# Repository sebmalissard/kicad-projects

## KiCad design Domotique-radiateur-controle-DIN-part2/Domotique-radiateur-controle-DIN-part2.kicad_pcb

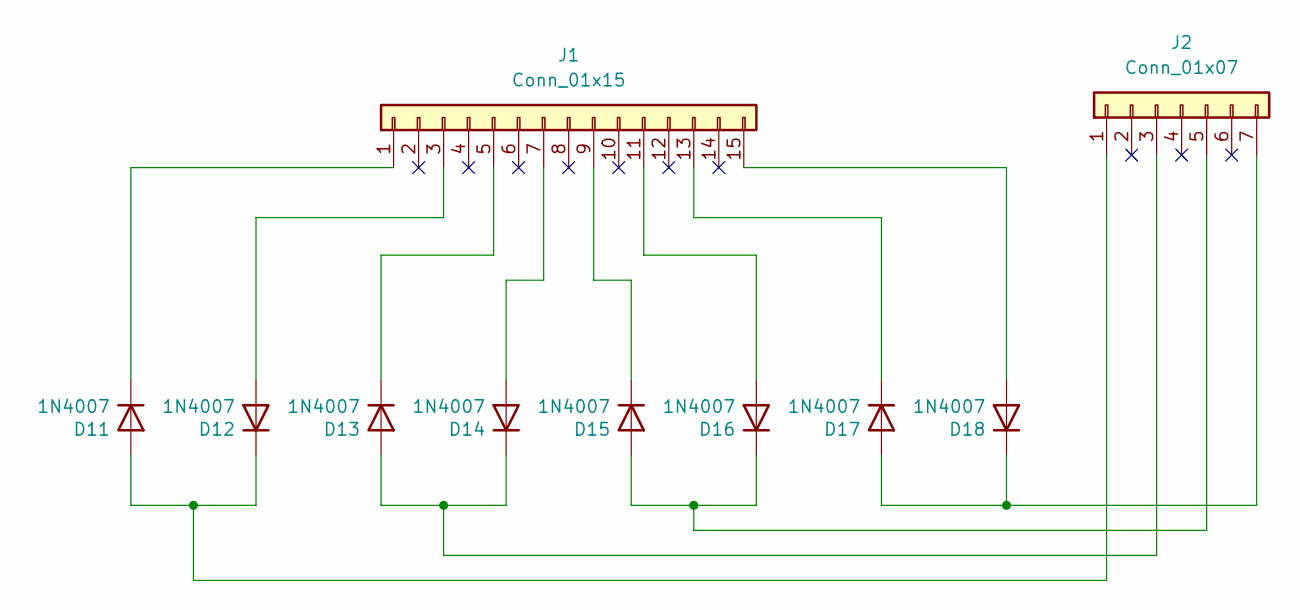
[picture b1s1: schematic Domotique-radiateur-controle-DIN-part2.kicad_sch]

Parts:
D11, D12, D13, D14, D15, D16, D17, D18: 1N4007; D_DO-41_SOD81_P7.62mm_Horizontal
J1: Conn_01x15; PinHeader_1x15_P2.54mm_Vertical
J2: Conn_01x07; PinHeader_1x07_P2.54mm_Vertical

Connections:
unnamed: D11.2 (A), D12.1 (K), J2.1
unnamed: D11.1 (K), J1.1
unnamed: D12.2 (A), J1.3
unnamed: D13.2 (A), D14.1 (K), J2.3
unnamed: D13.1 (K), J1.5
unnamed: D14.2 (A), J1.7
unnamed: D15.2 (A), D16.1 (K), J2.5
unnamed: D15.1 (K), J1.9
unnamed: D16.2 (A), J1.11
unnamed: D17.2 (A), D18.1 (K), J2.7
unnamed: D17.1 (K), J1.13
unnamed: D18.2 (A), J1.15

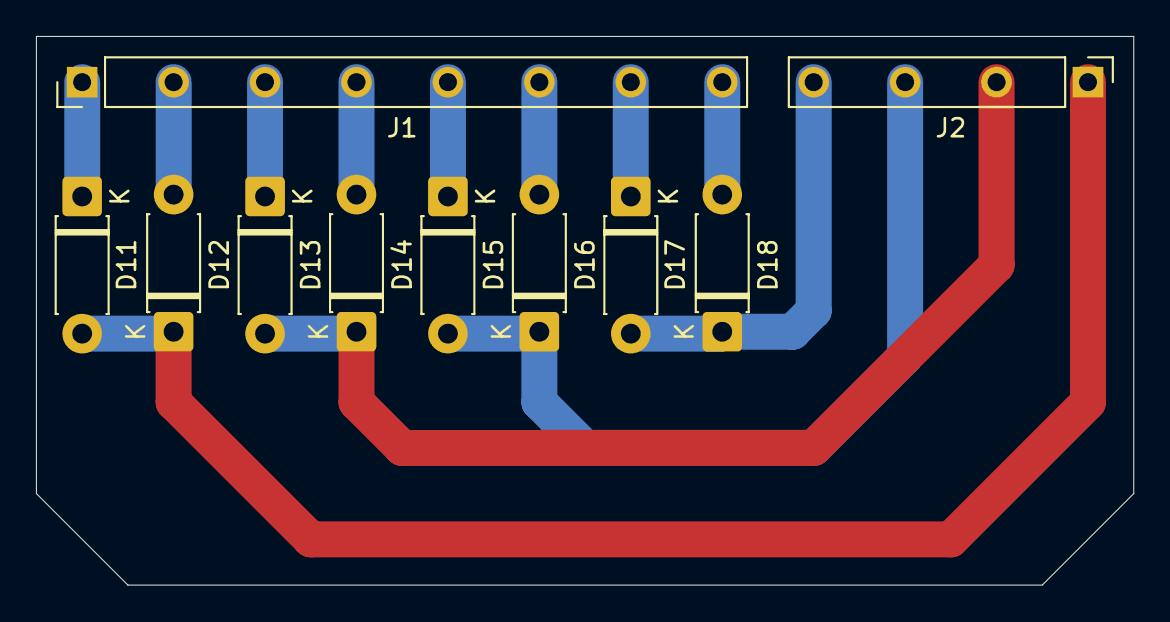
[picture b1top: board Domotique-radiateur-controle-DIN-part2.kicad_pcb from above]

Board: 2 copper layers, 61.0 x 30.5 mm, 10 parts (0 on the bottom side), 12 nets.

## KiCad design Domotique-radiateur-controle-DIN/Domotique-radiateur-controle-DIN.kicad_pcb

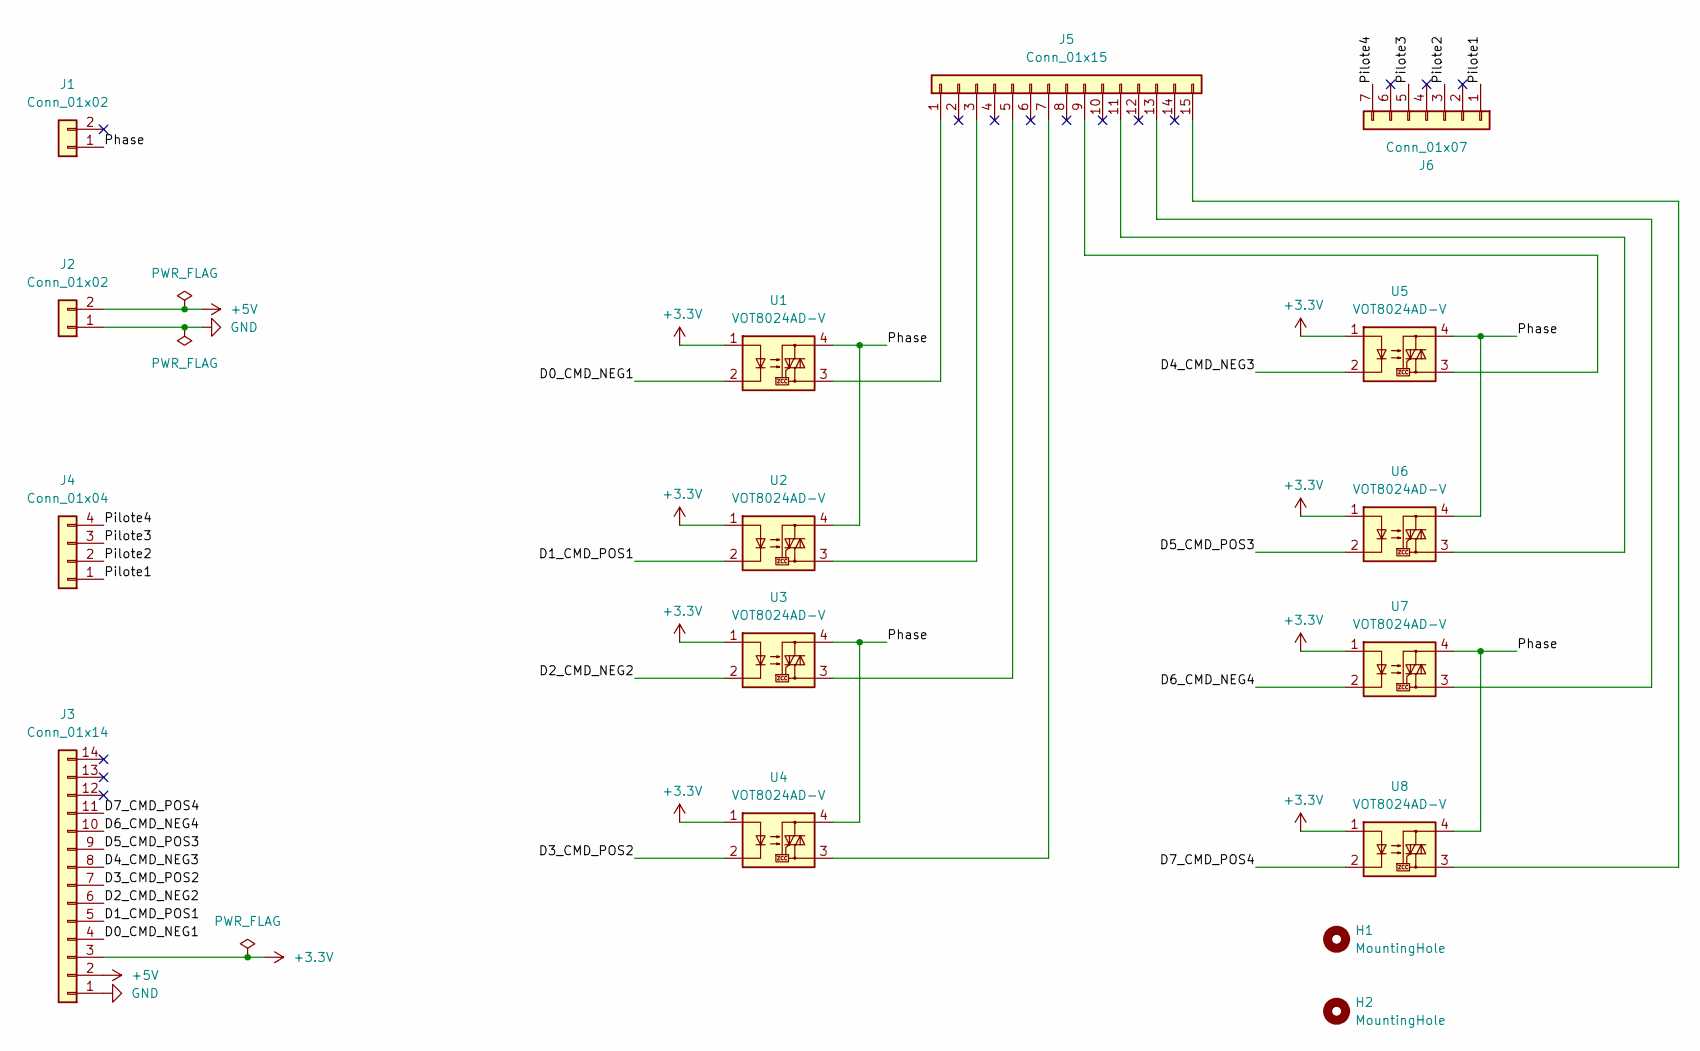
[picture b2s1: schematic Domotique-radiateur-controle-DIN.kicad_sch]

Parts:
H1, H2: MountingHole; MountingHole_3.2mm_M3
J1, J2: Conn_01x02; TerminalBlock_MetzConnect_Type055_RT01502HDWU_1x02_P5.00mm_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
J3: Conn_01x14; PinSocket_1x14_P2.54mm_Vertical
J4: Conn_01x04; TerminalBlock_MetzConnect_Type055_RT01504HDWU_1x04_P5.00mm_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
J5: Conn_01x15; PinHeader_1x15_P2.54mm_Vertical
J6: Conn_01x07; PinHeader_1x07_P2.54mm_Vertical
U1, U2, U3, U4, U5, U6, U7, U8: VOT8024AD-V; DIP-4_L6.5-W4.6-P2.54-LS7.6-BL; MPN VOT8024AD-V; LCSC Part C7149076

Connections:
+3.3V: J3.3, U1.1, U2.1, U3.1, U4.1, U5.1, U6.1, U7.1, U8.1
+5V: J2.2, J3.2
/D0_CMD_NEG1: J3.4, U1.2
/D1_CMD_POS1: J3.5, U2.2
/D2_CMD_NEG2: J3.6, U3.2
/D3_CMD_POS2: J3.7, U4.2
/D4_CMD_NEG3: J3.8, U5.2
/D5_CMD_POS3: J3.9, U6.2
/D6_CMD_NEG4: J3.10, U7.2
/D7_CMD_POS4: J3.11, U8.2
/Phase: J1.1 (Pin_1_1), U1.4, U2.4, U3.4, U4.4, U5.4, U6.4, U7.4, U8.4
/Pilote1: J4.1, J6.1
/Pilote2: J4.2, J6.3
/Pilote3: J4.3, J6.5
/Pilote4: J4.4, J6.7
GND: J2.1, J3.1
unnamed: J5.1, U1.3
unnamed: J5.3, U2.3
unnamed: J5.5, U3.3
unnamed: J5.7, U4.3
unnamed: J5.9, U5.3
unnamed: J5.11, U6.3
unnamed: J5.13, U7.3
unnamed: J5.15, U8.3

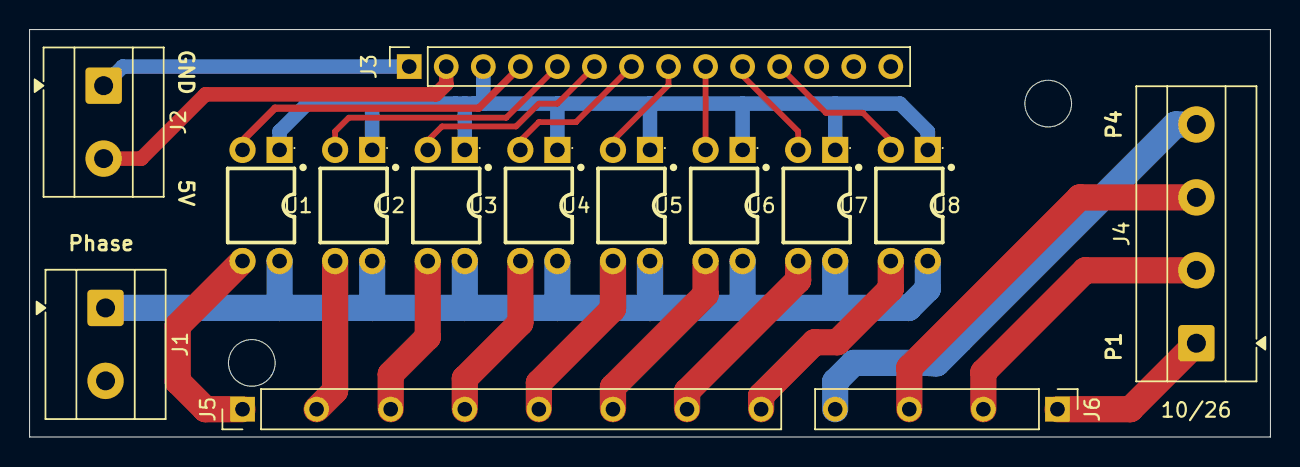
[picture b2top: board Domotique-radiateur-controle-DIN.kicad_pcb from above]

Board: 2 copper layers, 85.1 x 27.9 mm, 16 parts (0 on the bottom side), 24 nets.

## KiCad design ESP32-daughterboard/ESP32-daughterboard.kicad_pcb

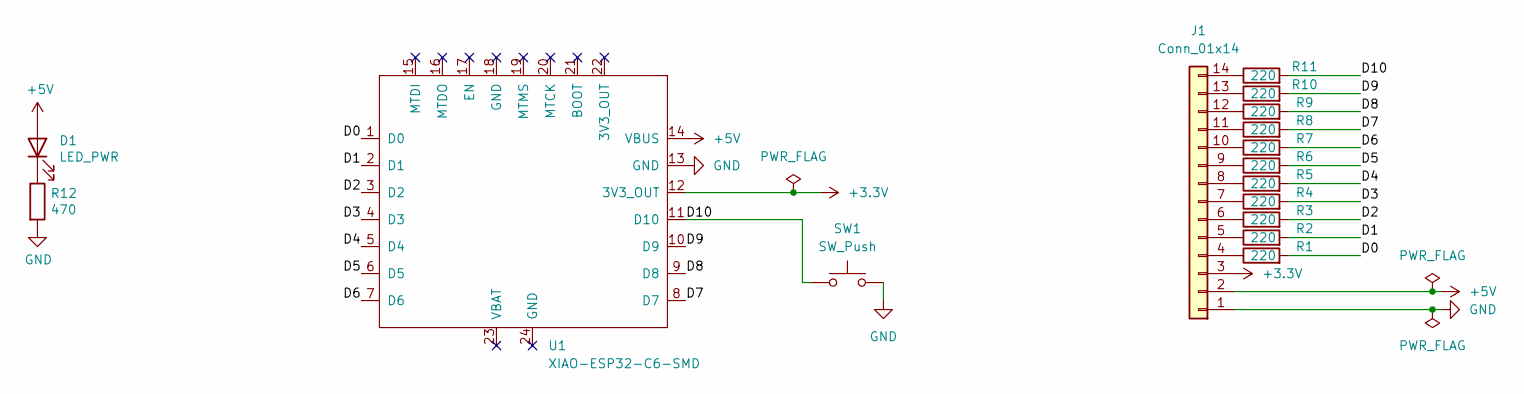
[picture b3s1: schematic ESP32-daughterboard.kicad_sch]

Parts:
D1: LED_PWR; LED_1206_3216Metric
J1: Conn_01x14; PinHeader_1x14_P2.54mm_Vertical
R1, R2, R3, R4, R5, R6, R7, R8, R9, R10, R11: 220; R_0805_2012Metric
R12: 470; R_Axial_DIN0207_L6.3mm_D2.5mm_P7.62mm_Horizontal
SW1: SW_Push
U1: XIAO-ESP32-C6-SMD; XIAO-ESP32-C6-DIP

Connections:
+3.3V: J1.3, U1.12 (3V3_OUT)
+5V: D1.2 (A), J1.2, U1.14 (VBUS)
/D0: R1.2, U1.1 (D0)
/D1: R2.2, U1.2 (D1)
/D2: R3.2, U1.3 (D2)
/D3: R4.2, U1.4 (D3)
/D4: R5.2, U1.5 (D4)
/D5: R6.2, U1.6 (D5)
/D6: R7.2, U1.7 (D6)
/D7: R8.2, U1.8 (D7)
/D8: R9.2, U1.9 (D8)
/D9: R10.2, U1.10 (D9)
/D10: R11.2, SW1.1, U1.11 (D10)
GND: J1.1, R12.2, SW1.2, U1.13 (GND)
unnamed: D1.1 (K), R12.1
unnamed: J1.4, R1.1
unnamed: J1.5, R2.1
unnamed: J1.6, R3.1
unnamed: J1.7, R4.1
unnamed: J1.8, R5.1
unnamed: J1.9, R6.1
unnamed: J1.10, R7.1
unnamed: J1.11, R8.1
unnamed: J1.12, R9.1
unnamed: J1.13, R10.1
unnamed: J1.14, R11.1

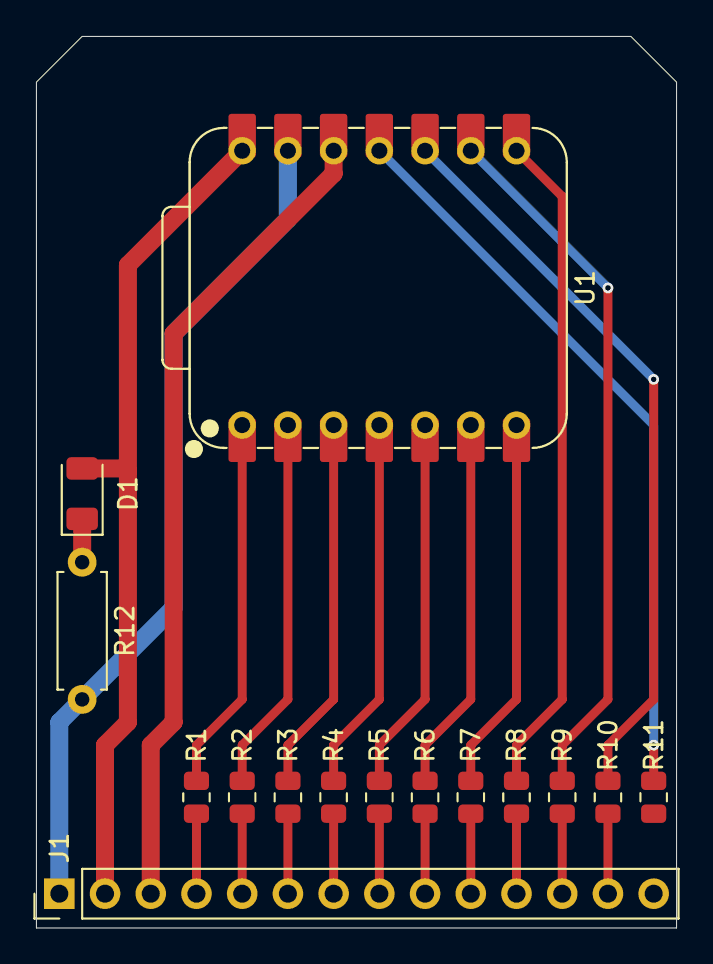
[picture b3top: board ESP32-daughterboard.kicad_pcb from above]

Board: 2 copper layers, 35.6 x 49.5 mm, 15 parts (0 on the bottom side), 26 nets.

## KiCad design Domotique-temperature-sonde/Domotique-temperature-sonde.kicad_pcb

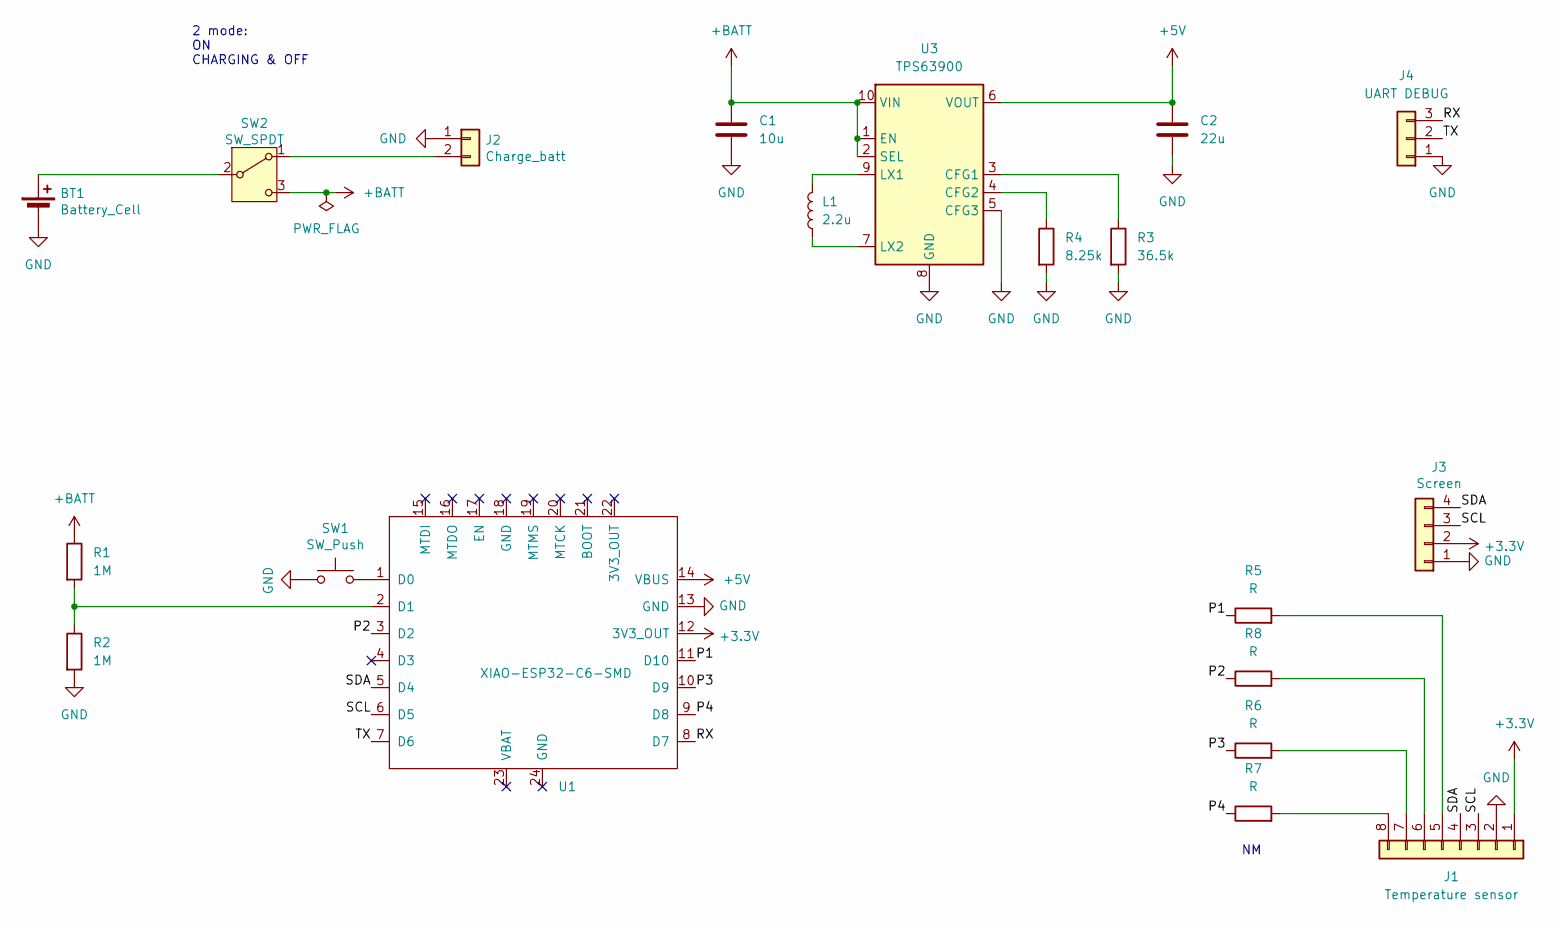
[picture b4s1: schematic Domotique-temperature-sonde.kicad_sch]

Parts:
BT1: Battery_Cell; Battery 18650
C1: 10u; C_0603_1608Metric; LCSC Part # C19702
C2: 22u; C_1206_3216Metric; LCSC Part # C12891
J1: Temperature sensor; PinSocket_1x08_P2.54mm_Horizontal
J2: Charge_batt; Molex_Micro-Fit_3.0_43650-0203_1x02_P3.00mm_Horizontal
J3: Screen; Display oled 0.91
J4: UART DEBUG; PinSocket_1x03_P2.54mm_Horizontal
L1: 2.2u; L_1008_2520Metric; LCSC Part # C576403
R1, R2: 1M; R_0805_2012Metric; LCSC Part # C17514
R3: 36.5k; R_0805_2012Metric; LCSC Part # C218534
R4: 8.25k; R_0805_2012Metric; LCSC Part # C374739
R5, R6, R7, R8: R; R_0805_2012Metric
SW1: SW_Push; SW_PUSH_6mm_H5mm
SW2: SW_SPDT; SW_Slide_SPDT_Angled_SK12F14VG4_3mm
U1: XIAO-ESP32-C6-SMD; XIAO-ESP32-C6-DIP
U3: TPS63900; WSON-10-1EP_2.5x2.5mm_P0.5mm_EP1.2x2mm_ThermalVias; LCSC Part # C1518762

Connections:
+3.3V: J1.1, J3.2, U1.12 (3V3_OUT)
+5V: C2.1, U1.14 (VBUS), U3.6 (VOUT)
+BATT: C1.1, R1.1, SW2.3 (C), U3.1 (EN), U3.2 (SEL), U3.10 (VIN)
/P1: R5.1, U1.11 (D10)
/P2: R8.1, U1.3 (D2)
/P3: R6.1, U1.10 (D9)
/P4: R7.1, U1.9 (D8)
/RX: J4.3, U1.8 (D7)
/SCL: J1.3, J3.3, U1.6 (D5)
/SDA: J1.4, J3.4, U1.5 (D4)
/TX: J4.2, U1.7 (D6)
GND: BT1.2 (-), C1.2, C2.2, J1.2, J2.1, J3.1, J4.1, R2.2, R3.2, R4.2, SW1.1, U1.13 (GND), U3.5 (CFG3), U3.8 (GND), U3.11 (GND)
unnamed: BT1.1 (+), SW2.2 (B)
unnamed: J1.5, R5.2
unnamed: J1.6, R8.2
unnamed: J1.7, R6.2
unnamed: J1.8, R7.2
unnamed: J2.2, SW2.1 (A)
unnamed: SW1.2, U1.1 (D0)
unnamed: R1.2, R2.1, U1.2 (D1)
unnamed: R3.1, U3.3 (CFG1)
unnamed: R4.1, U3.4 (CFG2)
unnamed: L1.2, U3.9 (LX1)
unnamed: L1.1, U3.7 (LX2)

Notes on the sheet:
2 mode: ON CHARGING & OFF

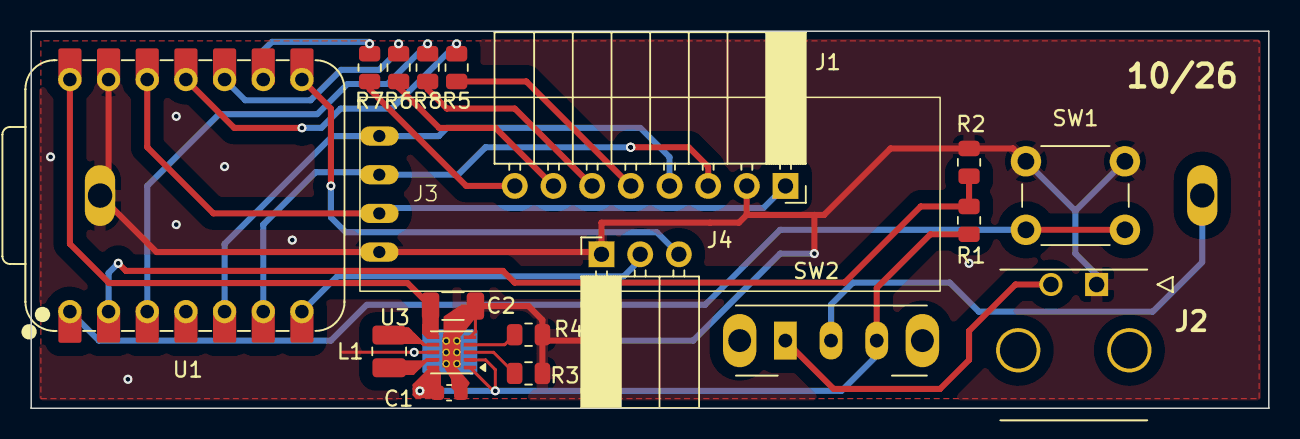
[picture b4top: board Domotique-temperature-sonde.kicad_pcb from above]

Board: 2 copper layers, 81.3 x 24.8 mm, 20 parts (1 on the bottom side), 24 nets.

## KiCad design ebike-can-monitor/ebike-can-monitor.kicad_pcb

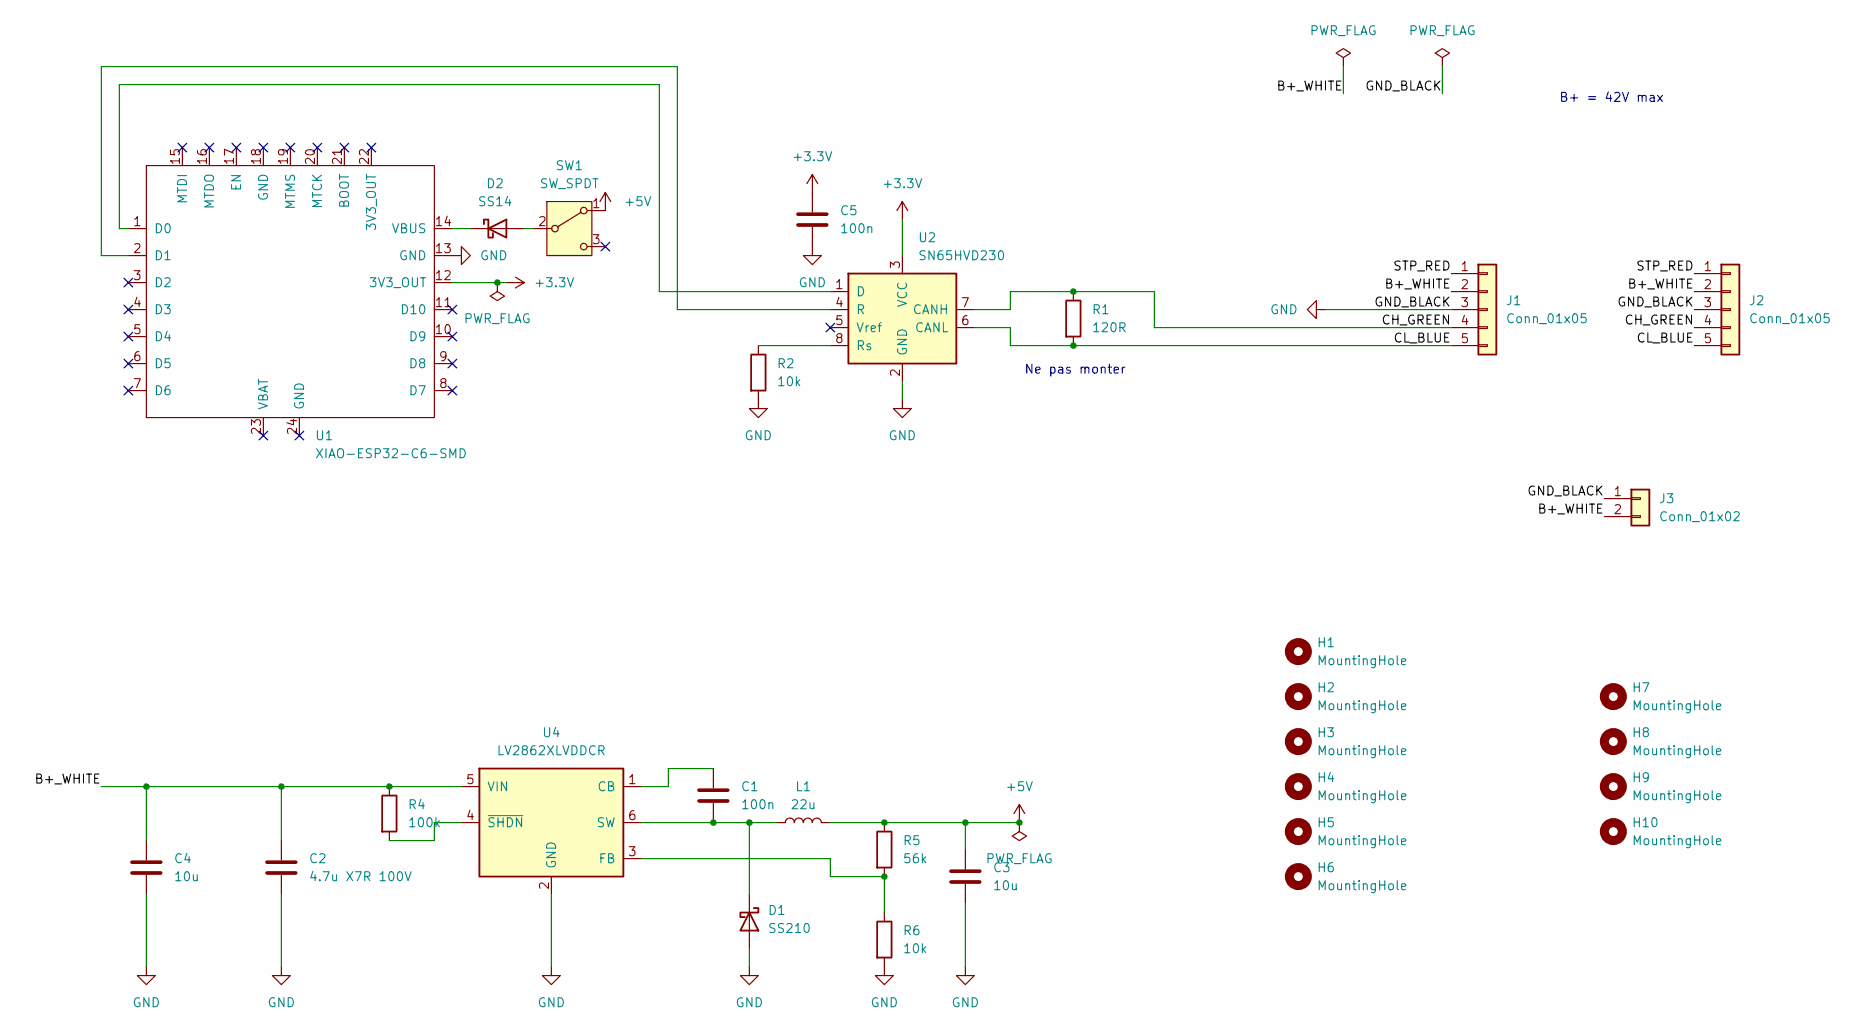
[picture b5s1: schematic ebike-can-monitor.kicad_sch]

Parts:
C1, C5: 100n; C_0805_2012Metric; LCSC C28233
C2: 4.7u X7R 100V; C_1206_3216Metric; LCSC C29823
C3, C4: 10u; C_1206_3216Metric; LCSC C13585
D1: SS210; D_SMA; LCSC C14996
D2: SS14; D_SMA; LCSC C2480
H1, H2, H3, H4, H5, H6, H7, H8, H9, H10: MountingHole; MountingHole_3.2mm_M3
J1, J2: Conn_01x05; PinHeader_1x05_P2.54mm_Vertical
J3: Conn_01x02; Molex_Micro-Fit_3.0_43650-0203_1x02_P3.00mm_Horizontal
L1: 22u; IND-SMD_L4.0-W4.0_LVF4040XX; LCSC C910042
R1: 120R; R_1206_3216Metric
R2, R6: 10k; R_0603_1608Metric; LCSC C25804
R4: 100k; R_0603_1608Metric; LCSC C25803
R5: 56k; R_0603_1608Metric; LCSC C23206
SW1: SW_SPDT; SW_Slide_SPDT_Straight_2D00G_3mm
U1: XIAO-ESP32-C6-SMD; XIAO-ESP32-C6-DIP
U2: SN65HVD230; SOIC-8_3.9x4.9mm_P1.27mm; LCSC C12084
U4: LV2862XLVDDCR; SOT-23-6; LCSC C3200285

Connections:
+3.3V: C5.1, U1.12 (3V3_OUT), U2.3 (VCC)
+5V: C3.1, L1.2, R5.1, SW1.1 (A)
/B+_WHITE: C2.1, C4.1, J1.2, J2.2, J3.2, R4.1, U4.5 (VIN)
/CH_GREEN: J1.4, J2.4, R1.1, U2.7 (CANH)
/CL_BLUE: J1.5, J2.5, R1.2, U2.6 (CANL)
/STP_RED: J1.1, J2.1
GND: C2.2, C3.2, C4.2, C5.2, D1.2 (A), J1.3, J2.3, J3.1, R2.2, R6.2, U1.13 (GND), U2.2 (GND), U4.2 (GND)
unnamed: C1.2, D1.1 (K), L1.1, U4.6 (SW)
unnamed: D2.2 (A), SW1.2 (B)
unnamed: D2.1 (K), U1.14 (VBUS)
unnamed: U1.1 (D0), U2.1 (D)
unnamed: U1.2 (D1), U2.4 (R)
unnamed: R2.1, U2.8 (Rs)
unnamed: C1.1, U4.1 (CB)
unnamed: R5.2, R6.1, U4.3 (FB)
unnamed: R4.2, U4.4 (~SHDN)

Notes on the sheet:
B+ = 42V max
Ne pas monter

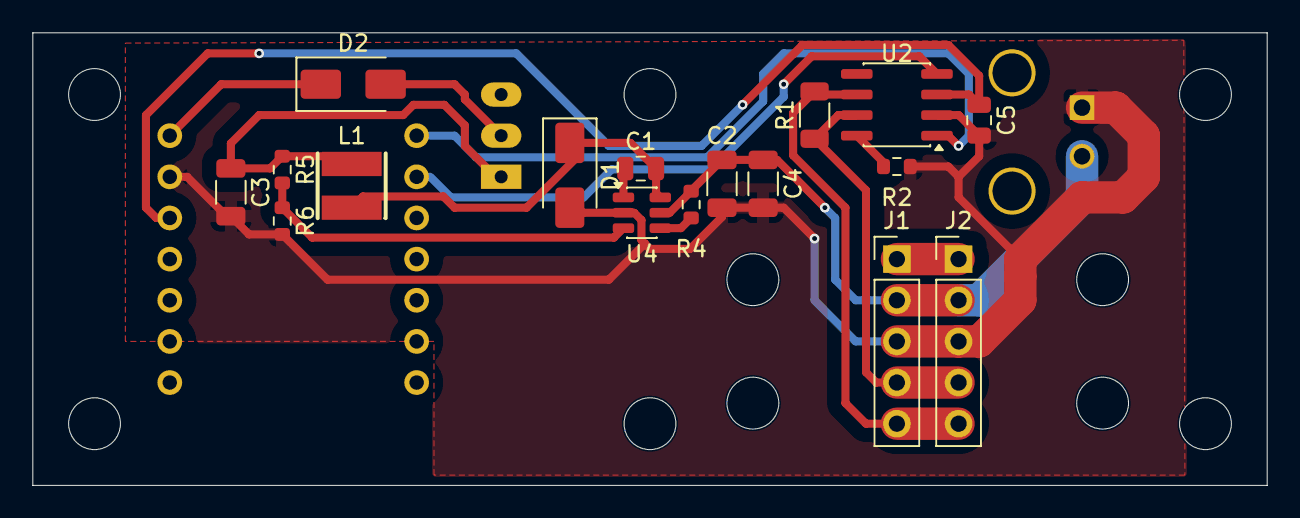
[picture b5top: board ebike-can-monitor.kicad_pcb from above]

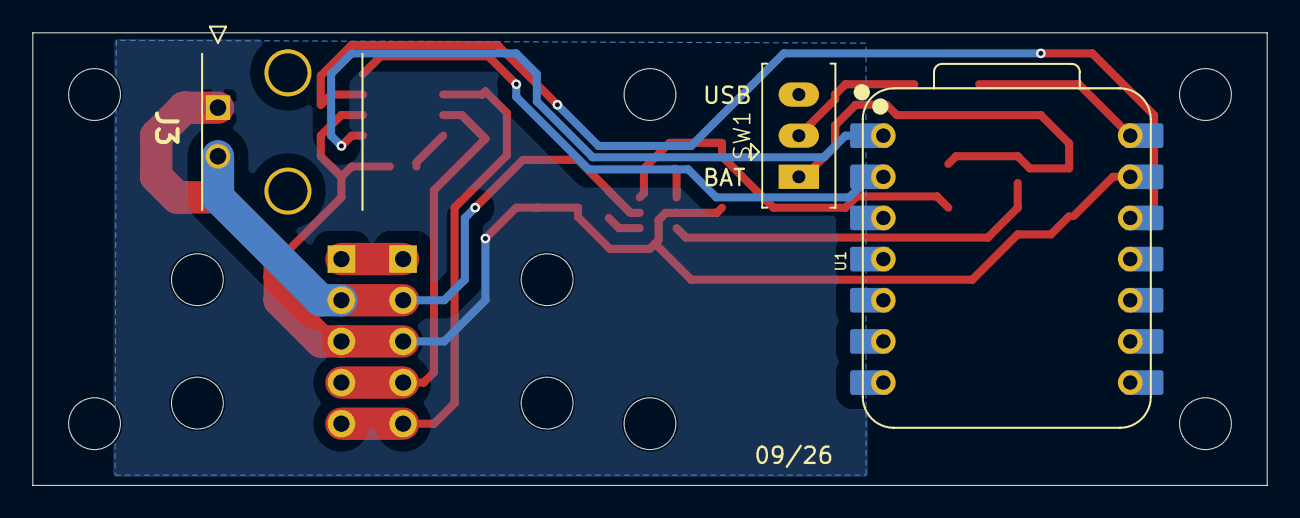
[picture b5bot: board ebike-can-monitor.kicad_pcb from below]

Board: 2 copper layers, 76.2 x 27.9 mm, 30 parts (3 on the bottom side), 16 nets.

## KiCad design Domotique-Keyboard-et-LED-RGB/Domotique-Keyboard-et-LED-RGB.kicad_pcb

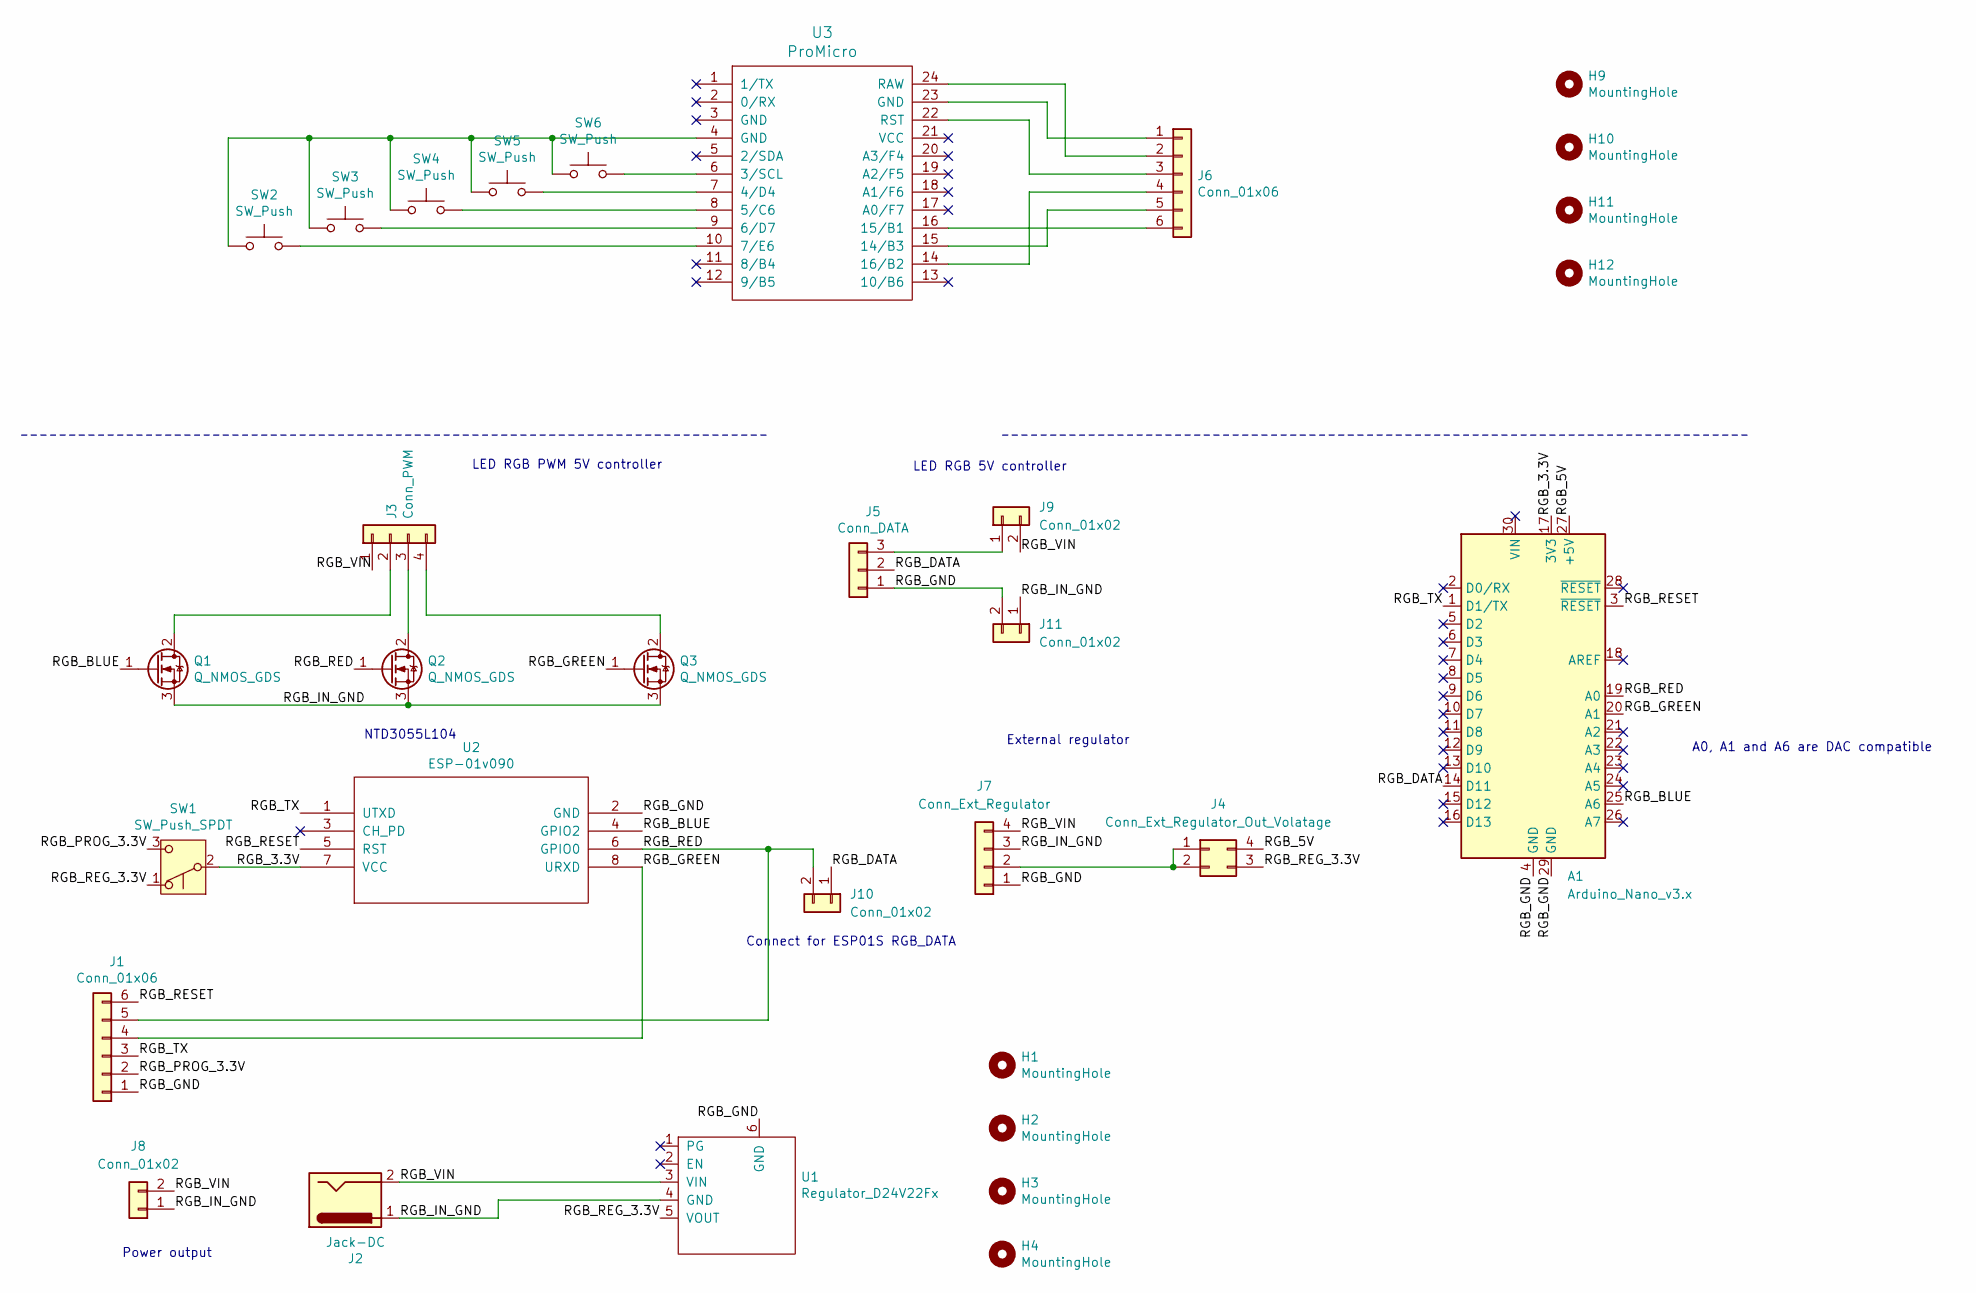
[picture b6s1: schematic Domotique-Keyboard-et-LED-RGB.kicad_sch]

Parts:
A1: Arduino_Nano_v3.x; Arduino_Nano
H1, H2, H3, H4, H9, H10, H11, H12: MountingHole; MountingHole_2.2mm_M2
J1, J6: Conn_01x06; Molex_SL_70555-0040_1x06_P2.54mm_Horizontal
J2: Jack-DC; TerminalBlock_Phoenix_MKDS-1,5-2-5.08_1x02_P5.08mm_Horizont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
J3: Conn_PWM; Molex_Micro-Fit_3.0_43650-0403_1x04_P3.00mm_Horizontal
J4: Conn_Ext_Regulator_Out_Volatage; PinHeader_2x02_P2.54mm_Vertical
J5: Conn_DATA; Molex_Micro-Fit_3.0_43650-0303_1x04_P3.00mm_Horizontal
J7: Conn_Ext_Regulator; Molex_Micro-Fit_3.0_43650-0403_1x04_P3.00mm_Horizontal
J8: Conn_01x02; TerminalBlock_Phoenix_MKDS-1,5-2-5.08_1x02_P5.08mm_Horizont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
J9, J10, J11: Conn_01x02; PinHeader_1x02_P2.54mm_Vertical
Q1, Q2, Q3: Q_NMOS_GDS; TO-262-3_Vertical
SW1: SW_Push_SPDT; SW_Slide_SPDT_Angled_SK12F14VG4_3mm
SW2, SW3, SW4, SW5, SW6: SW_Push; SW_PUSH_12mm_H4.5mm
U1: Regulator_D24V22Fx; Pololu_reg19a
U2: ESP-01v090; ESP-01
U3: ProMicro

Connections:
/RGB_3.3V: A1.17 (3V3), SW1.2 (B), U2.7 (VCC)
/RGB_5V: A1.27 (+5V), J4.4
/RGB_BLUE: A1.25 (A6), Q1.1 (G), U2.4 (GPIO2)
/RGB_DATA: A1.14 (D11), J5.2, J10.1
/RGB_GND: A1.4 (GND), A1.29 (GND), J1.1, J5.1, J7.1, J11.2, U1.6 (GND), U2.2 (GND)
/RGB_GREEN: A1.20 (A1), J1.4, Q3.1 (G), U2.8 (URXD)
/RGB_IN_GND: J2.1, J7.3, J8.1, J11.1, Q1.3 (S), Q2.3 (S), Q3.3 (S), U1.4 (GND)
/RGB_PROG_3.3V: J1.2, SW1.3 (C)
/RGB_RED: A1.19 (A0), J1.5, J10.2, Q2.1 (G), U2.6 (GPIO0)
/RGB_REG_3.3V: J4.3, SW1.1 (A), U1.5 (VOUT)
/RGB_RESET: A1.3 (~RESET), J1.6, U2.5 (RST)
/RGB_TX: A1.1 (D1/TX), J1.3, U2.1 (UTXD)
/RGB_VIN: J2.2, J3.1, J7.4, J8.2, J9.2, U1.3 (VIN)
unnamed: J3.2, Q1.2 (D)
unnamed: J3.3, Q2.2 (D)
unnamed: J3.4, Q3.2 (D)
unnamed: J4.1, J4.2, J7.2
unnamed: J5.3, J9.1
unnamed: J6.1, U3.23 (GND)
unnamed: J6.2, U3.24 (RAW)
unnamed: J6.3, U3.22 (RST)
unnamed: J6.4, U3.14 (16/B2)
unnamed: J6.5, U3.15 (14/B3)
unnamed: J6.6, U3.16 (15/B1)
unnamed: SW2.1, SW3.1, SW4.1, SW5.1, SW6.1, U3.4 (GND)
unnamed: SW6.2, U3.6 (3/SCL)
unnamed: SW5.2, U3.7 (4/D4)
unnamed: SW4.2, U3.8 (5/C6)
unnamed: SW3.2, U3.9 (6/D7)
unnamed: SW2.2, U3.10 (7/E6)

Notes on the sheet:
NTD3055L104
LED RGB 5V controller
A0, A1 and A6 are DAC compatible
Power output
External regulator
LED RGB PWM 5V controller
Connect for ESP01S RGB_DATA

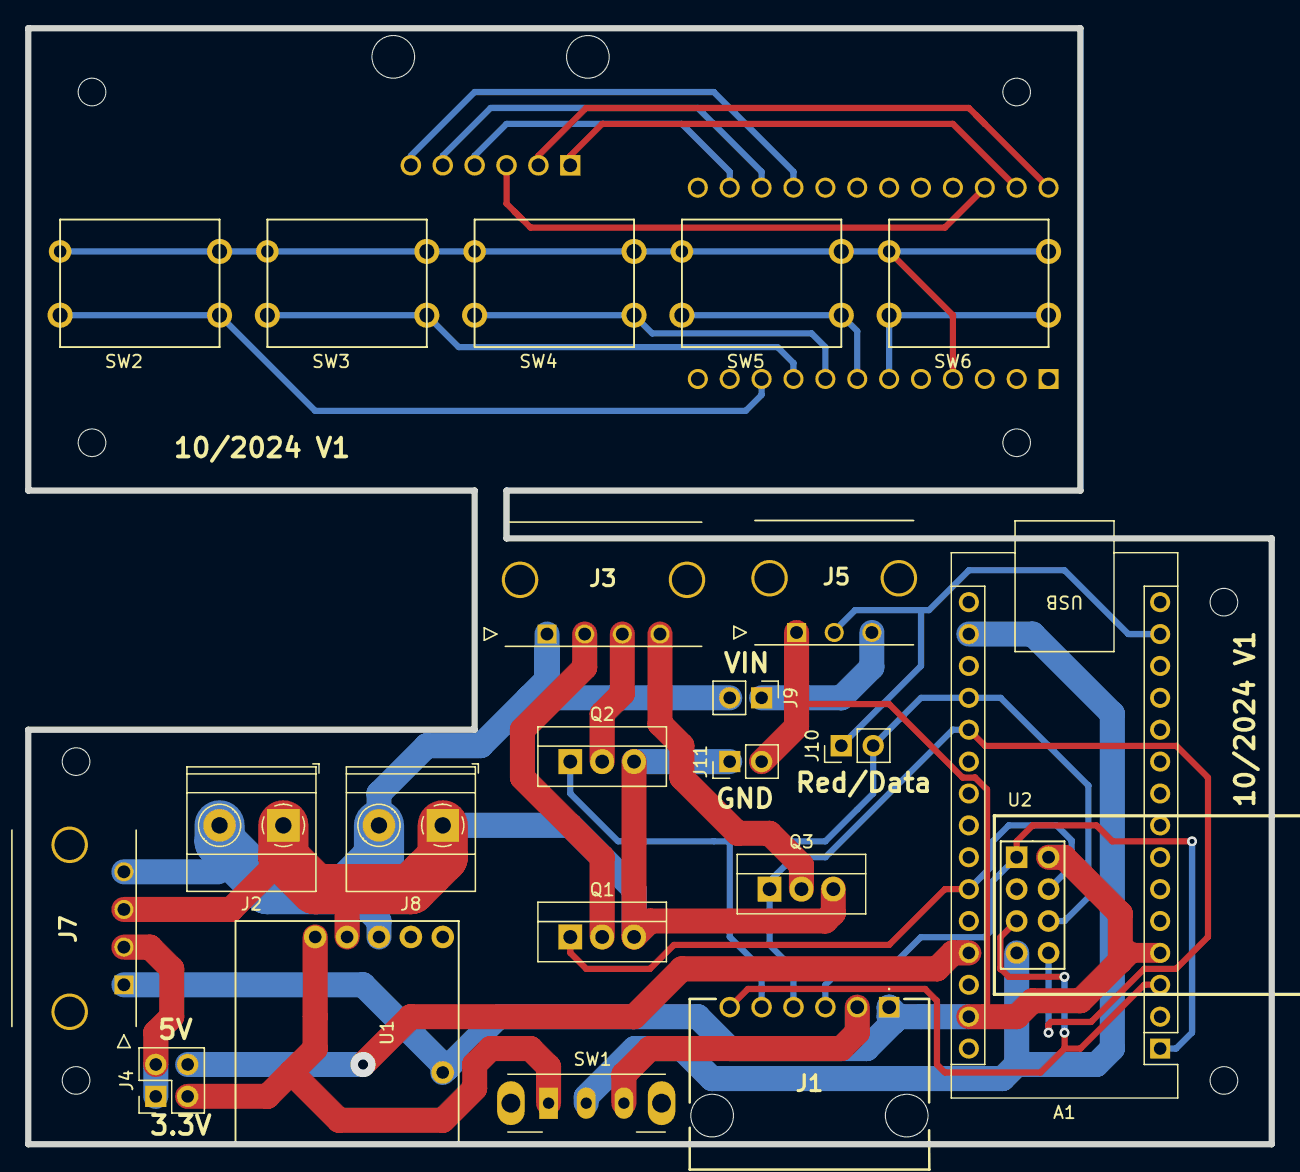
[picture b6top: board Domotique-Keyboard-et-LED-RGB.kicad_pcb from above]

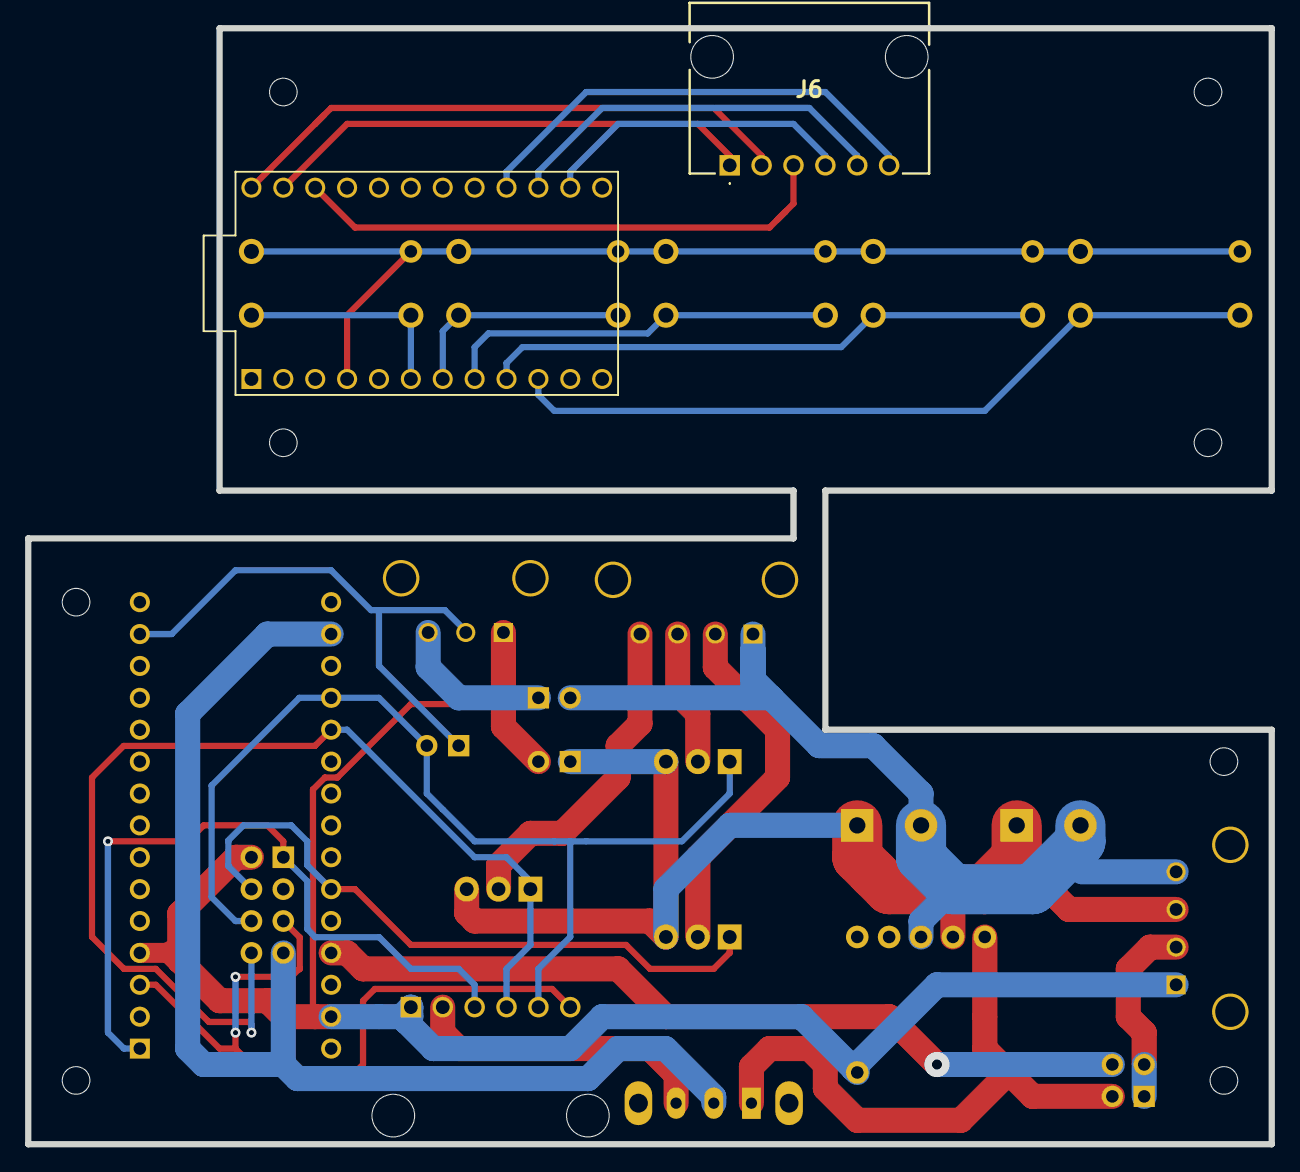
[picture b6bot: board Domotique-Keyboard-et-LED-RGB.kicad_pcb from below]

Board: 2 copper layers, 99.1 x 88.9 mm, 32 parts (2 on the bottom side), 30 nets.
